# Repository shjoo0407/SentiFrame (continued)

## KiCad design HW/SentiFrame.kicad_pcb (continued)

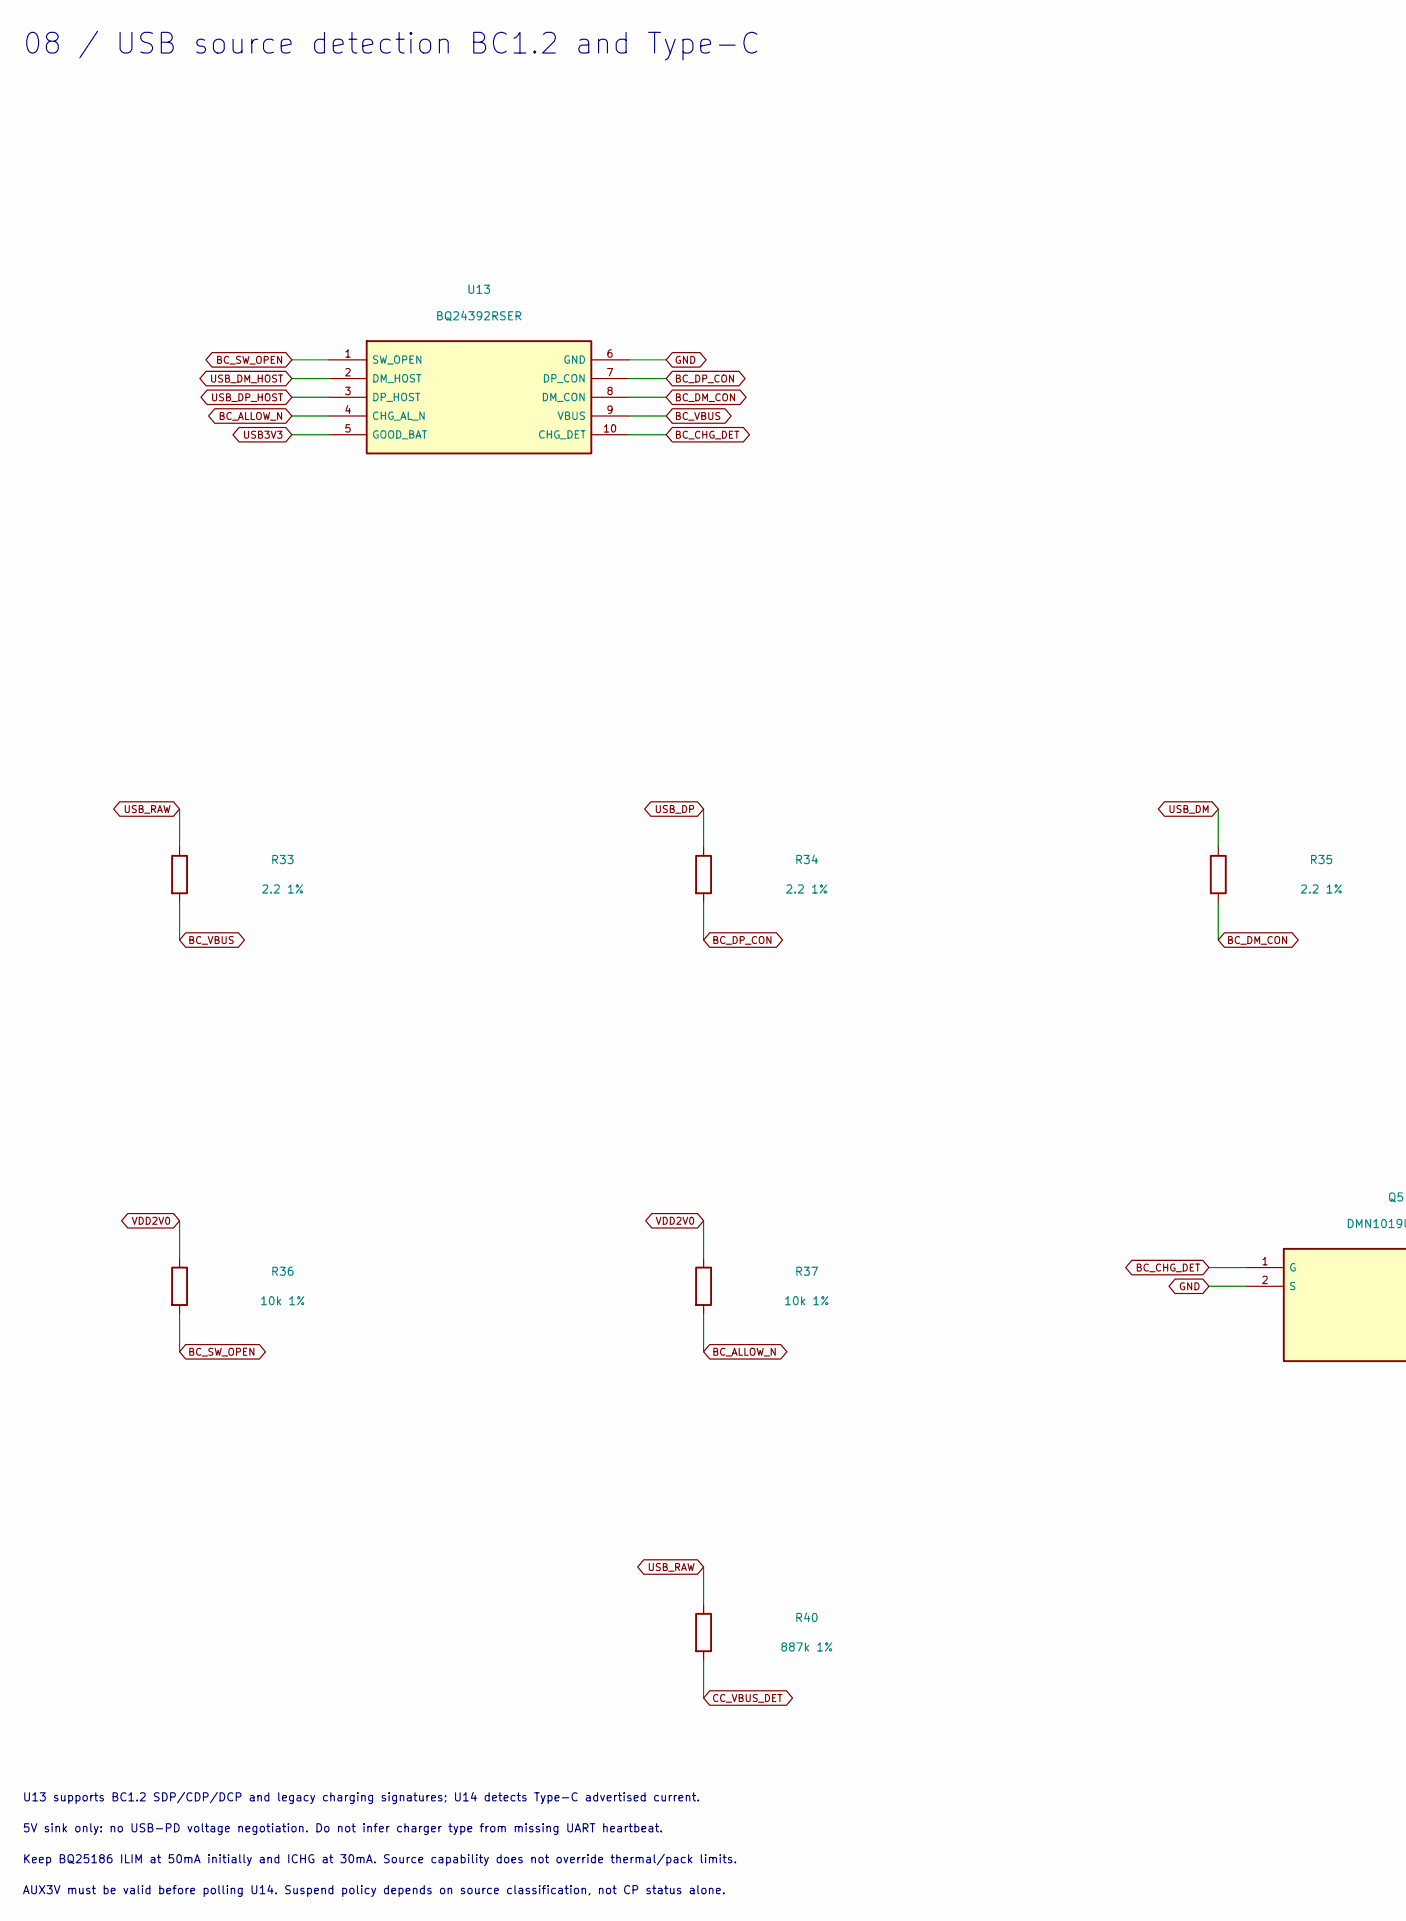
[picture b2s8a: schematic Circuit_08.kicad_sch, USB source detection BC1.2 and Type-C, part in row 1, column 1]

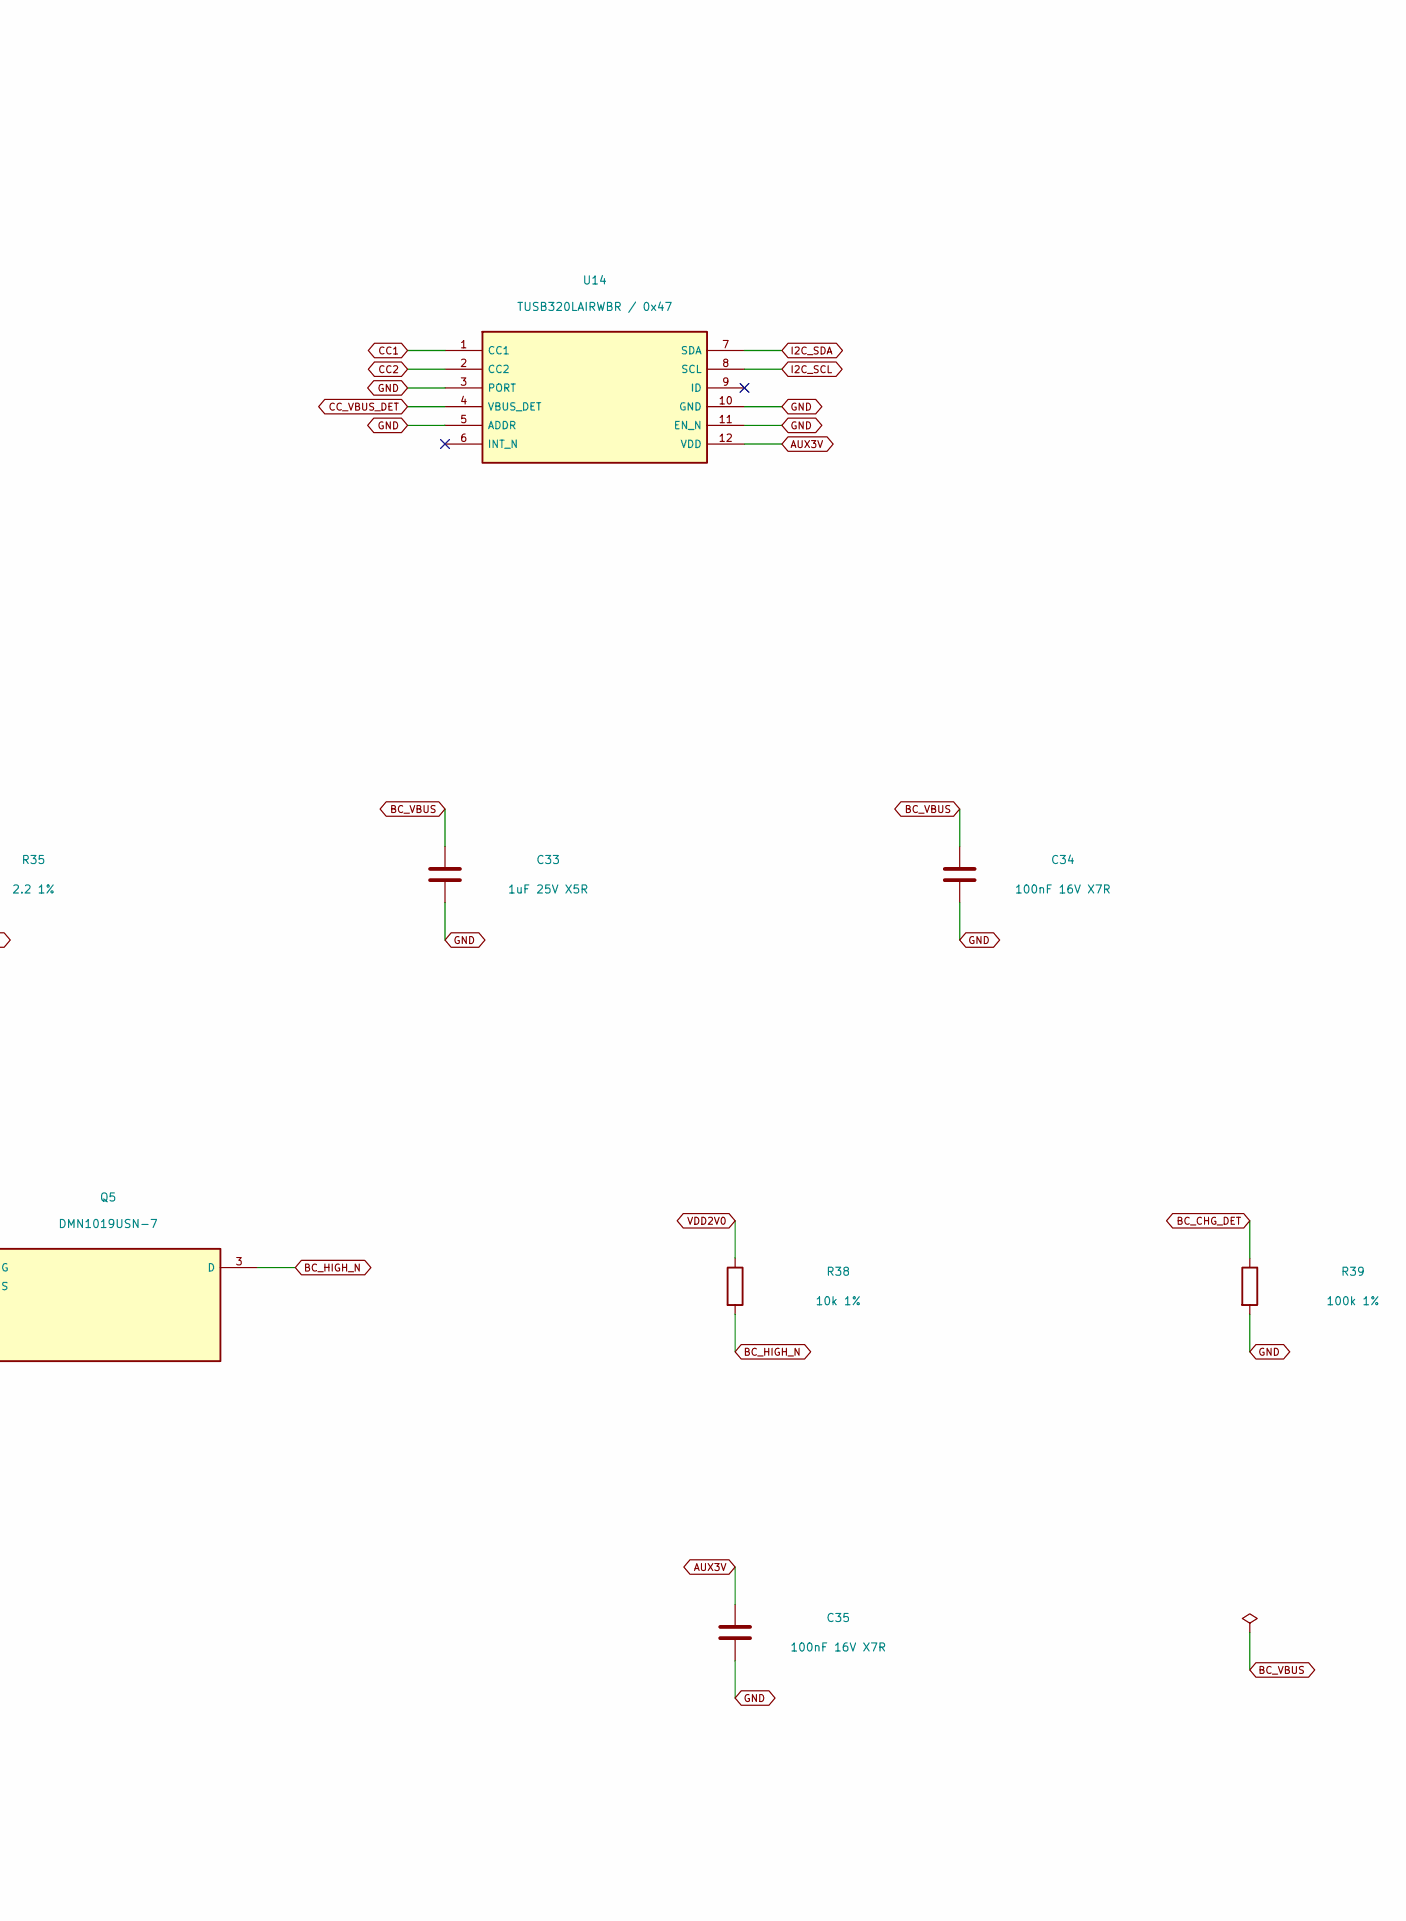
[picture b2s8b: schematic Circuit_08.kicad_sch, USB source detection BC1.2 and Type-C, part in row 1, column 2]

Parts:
C33: 1uF 25V X5R; C_0603_1608Metric; MPN C1608X5R1E105K080AC
C34, C35: 100nF 16V X7R; C_0402_1005Metric; MPN C1005X7R1C104K050BC
Q5: DMN1019USN-7; SC-59; MPN DMN1019USN-7
R33, R34, R35: 2.2 1%; R_0402_1005Metric; MPN RC0402FR-072R2L
R36, R37, R38: 10k 1%; R_0402_1005Metric; MPN RC0402FR-0710KL
R39: 100k 1%; R_0402_1005Metric; MPN RC0402FR-07100KL
R40: 887k 1%; R_0402_1005Metric; MPN RC0402FR-07887KL
U13: BQ24392RSER; Texas_UQFN-10_1.5x2mm_P0.5mm; MPN BQ24392RSER
U14: TUSB320LAIRWBR / 0x47; Texas_X2QFN-12_1.6x1.6mm_P0.4mm; MPN TUSB320LAIRWBR

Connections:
AUX3V: C35.1, U14.12 (VDD); also elsewhere on the board
BC_ALLOW_N: R37.2, U13.4 (CHG_AL_N); also elsewhere on the board
BC_CHG_DET: Q5.1 (G), R39.1, U13.10 (CHG_DET)
BC_DM_CON: R35.2, U13.8 (DM_CON)
BC_DP_CON: R34.2, U13.7 (DP_CON)
BC_HIGH_N: Q5.3 (D), R38.2; also elsewhere on the board
BC_SW_OPEN: R36.2, U13.1 (SW_OPEN); also elsewhere on the board
BC_VBUS: C33.1, C34.1, R33.2, U13.9 (VBUS)
CC1: U14.1 (CC1); also elsewhere on the board
CC2: U14.2 (CC2); also elsewhere on the board
CC_VBUS_DET: R40.2, U14.4 (VBUS_DET)
GND: C33.2, C34.2, C35.2, Q5.2 (S), R39.2, U13.6 (GND), U14.3 (PORT), U14.5 (ADDR), U14.10 (GND), U14.11 (EN_N); also elsewhere on the board
I2C_SCL: U14.8 (SCL); also elsewhere on the board
I2C_SDA: U14.7 (SDA); also elsewhere on the board
USB3V3: U13.5 (GOOD_BAT); also elsewhere on the board
USB_DM: R35.1; also elsewhere on the board
USB_DM_HOST: U13.2 (DM_HOST); also elsewhere on the board
USB_DP: R34.1; also elsewhere on the board
USB_DP_HOST: U13.3 (DP_HOST); also elsewhere on the board
USB_RAW: R33.1, R40.1; also elsewhere on the board
VDD2V0: R36.1, R37.1, R38.1; also elsewhere on the board

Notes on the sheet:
08 / USB source detection BC1.2 and Type-C
U13 supports BC1.2 SDP/CDP/DCP and legacy charging signatures; U14 detects Type-C advertised current.
5V sink only: no USB-PD voltage negotiation. Do not infer charger type from missing UART heartbeat.
Keep BQ25186 ILIM at 50mA initially and ICHG at 30mA. Source capability does not override thermal/pack limits.
AUX3V must be valid before polling U14. Suspend policy depends on source classification, not CP status alone.

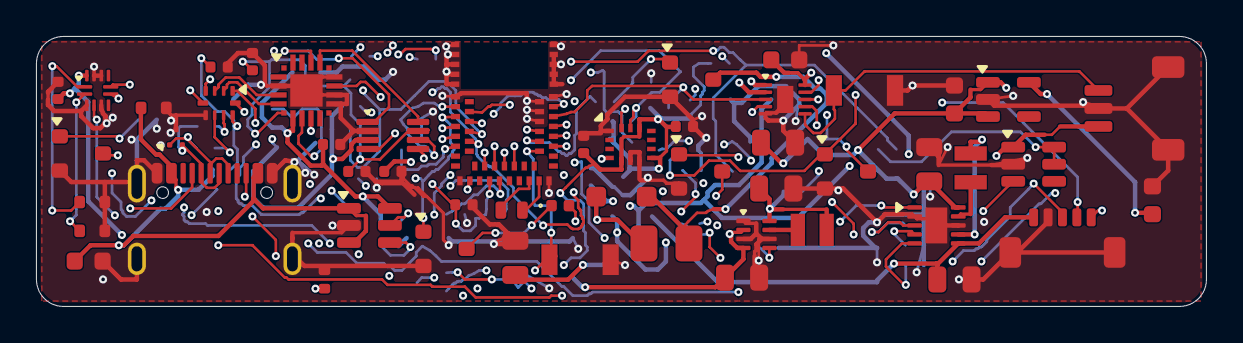
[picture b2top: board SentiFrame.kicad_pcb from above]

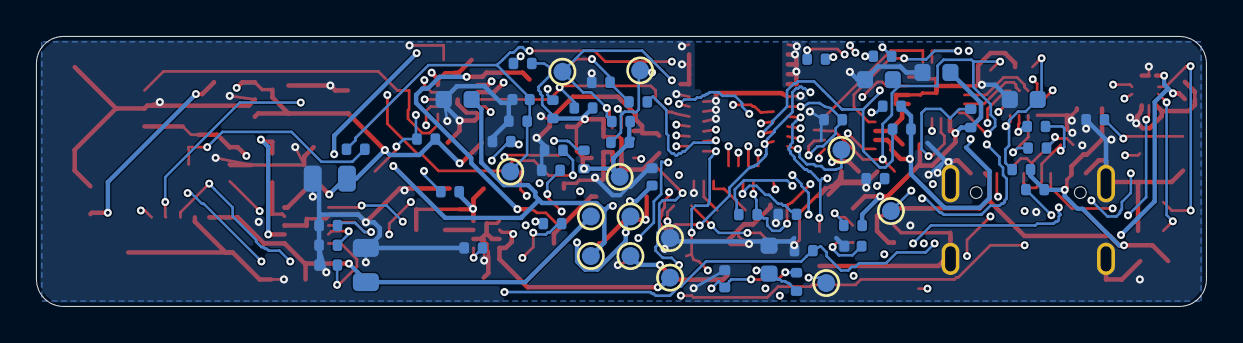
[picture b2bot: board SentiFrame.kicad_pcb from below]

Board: 4 copper layers, 65.0 x 15.0 mm, 113 parts (61 on the bottom side), 66 nets.

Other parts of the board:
C5, C6: 100nF 16V X7R; C_0402_1005Metric
J4: SM05B-SURS-TF / PPG MAIN; JST_SUR_SM05B-SURS-TF_J4_SilkClearance
R13: 10k 1%; R_0402_1005Metric
R14: 100k 1%; R_0402_1005Metric
U2: BMI270 / I2C 0x68; BMI270_LGA14_DS00008

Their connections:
GND: C5.2, C6.2, J4.2, J4.MP, R14.2, U2.1, U2.6, U2.7; also elsewhere on the board
I2C_SCL: J4.4, U2.13; also elsewhere on the board
I2C_SDA: J4.3, U2.14; also elsewhere on the board
IMU_INT: R14.1, U2.4; also elsewhere on the board
PPG5V: J4.1; also elsewhere on the board
PPG_INT_N: J4.5, R13.2; also elsewhere on the board
VDD2V0: C5.1, C6.1, R13.1, U2.5, U2.8, U2.12; also elsewhere on the board
